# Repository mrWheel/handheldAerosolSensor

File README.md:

# Low-Power Air Quality Monitor (SPS30 + E-Paper)

## Disclaimer
This software is developed incrementally. That means I have no clear idea how it works (though it *mostly* does).

If you have questions about this software, it will probably take you just as long to figure things out as it would take me. So I’d prefer that you investigate it yourself.

Having said that **Don’t Even Think About Using It**

Seriously. Don’t.

Building this design may injure or kill you during construction, burn your house down while in use, and then—just to be thorough—explode afterward.

This is **not** a joke. This project involves **lethal voltages**. If you are not a **qualified electronics engineer**, close this repository, step away from the soldering iron, and make yourself a cup of tea.

If you decide to ignore all of the above and build it anyway, you do so **entirely at your own risk**. You are fully responsible for taking proper safety precautions. I take **zero responsibility** for anything that happens—electrically, mechanically, chemically, spiritually, or otherwise.

Also, full disclosure: I am **not** a qualified electrical engineer. I provide **no guarantees**, **no warranties**, and **absolutely no assurance** that this design is correct, safe, or suitable for any purpose whatsoever.

# What it is
This project is a **battery-powered, low-power air quality monitor** based on:

- **ESP32 DEVKIT V1**
- **Sensirion SPS30** particulate matter sensor (I²C)
- **1.54" black/white e‑paper display (200×200)**
- **High-side power latch** using a P‑channel MOSFET + 2N7000 or BSS138
- **Single-cell Li‑ion (18650)** battery with DC/DC boost to 5 V

The system powers itself on with a button, performs a measurement cycle, updates the e‑paper display, and then **fully powers itself off** to achieve near-zero standby current.

---

## Features

- True hardware power-off (no sleep leakage)
- SPS30 warm-up with countdown on e‑paper
- Configurable number of measurement attempts
- **Only valid sensor samples are averaged**
- PM1.0 / PM2.5 / PM10 display
- Simple air-quality classification (PM2.5 based)
- Battery voltage and percentage display

---

## Measurement Flow

1. User presses power button
2. Power latch engages
3. E‑paper resets and shows status
4. SPS30 starts measurement
5. Warm-up delay (default: 15 s)
6. Up to `maxMetingen` measurement attempts
   - Only valid samples are accumulated
7. Average values are calculated
8. Results are shown on the e‑paper
9. SPS30 is stopped
10. Power latch is released (device turns fully off)

---

## Hardware Connections

### ESP32 DevKit V1 - Pin mapping for AerosolSensor

| ESP32 pin | DEVKIT V1 | Standaard functie              | AerosolSensor        | Opmerking |
|-----------|-----------|--------------------------------|----------------------|-----------|
| 25        | D25       | GPIO / DAC1                    | GPIO_PIN_LATCH       | Latch control (OUTPUT) |
| 33        | D33       | GPIO / ADC1_CH5 / Touch        | GPIO_PIN_SWITCH      | Switch input (INPUT_PULLUP), non-strapping |
| 34        | D34       | ADC1_CH6 (input-only)          | GPIO_PIN_BAT_ADC     | Battery ADC (input-only), ADC1 recommended |
| 21        | D21       | I2C SDA (typical)              | GPIO_PIN_SPS30_SDA   | SPS30 SDA |
| 22        | D22       | I2C SCL (typical)              | GPIO_PIN_SPS30_SCL   | SPS30 SCL |
| 16        | RX2       | Future Ext.                    | GPIO_PIN_SPS_UART_RX | Serial SPS module |
| 17        | TX2       | Future Ext.                    | GPIO_PIN_SPS_UART_TX | Serial SPS module | 
| 23        | D23       | VSPI MOSI (typical)            | GPIO_PIN_EPD_MOSI    | E-paper DIN (MOSI) |
| -1        | n.c.      | n.v.t.                         | GPIO_PIN_EPD_MISO    | Not connected on display |
| 18        | D18       | VSPI SCK (typical)             | GPIO_PIN_EPD_SCK     | E-paper CLK (SCK) |
| 27        | D27       | GPIO                           | GPIO_PIN_EPD_CS      | E-paper CS |
| 19        | D19       | e-Paper DC                     | GPIO_PIN_EPD_DC      | E-paper DC |
| 13        | D13       | e-Paper RST                    | GPIO_PIN_EPD_RST     | E-paper RST |
| 32        | D32       | GPIO / ADC1_CH4 / Touch        | GPIO_PIN_EPD_BUSY    | E-paper BUSY (INPUT_PULLUP), non-strapping |
| 14        | D14       | GPIO PWM Touch                 | GPIO_PIN_BUZZER_PWM  | Buzzer 

### Battery Measurement

- 100 kΩ / 100 kΩ divider from battery to D34
- Optional 100 nF capacitor from D34 to GND

---

## Software Stack

- **PlatformIO**
- **Arduino framework**
- **Libraries**
  - GxEPD2
  - Adafruit GFX
  - Adafruit BMP280 Library
  - Adafruit Unified Sensor
  - Sensirion SPS30 (GitHub)
  - safeTimers

---

## PlatformIO Configuration

```ini
; platformio.ini
;
;— ESP32 + Arduino framework
;— Pin choices avoid ESP32 strapping pins (GPIO0,2,4,5,12,15) and flash pins (GPIO6–11).
;— Battery ADC uses ADC1 (GPIO34) so it keeps working even if WiFi were enabled.
;— SPI uses VSPI defaults for ESP32: MOSI=23, MISO=19, SCK=18.

[platformio]
workspace_dir = .pio.nosync
default_envs = esp32dev

[env:esp32dev]
platform = espressif32
board = esp32dev
framework = arduino

monitor_speed = 115200
upload_speed = 921600

;-- do NOT use 0, 2, 4, 5, 12, 15 (Strapping pins) or 6–11 (Flash pins)
build_flags =
  ;==================== Power & user input ====================
  ;— Power latch control (OUTPUT)
  -D GPIO_PIN_LATCH=25

  ;— User pushbutton (INPUT_PULLUP, LOW = pressed)
  -D GPIO_PIN_SWITCH=33

  ;==================== Battery measurement ====================
  ;— Battery voltage divider ADC input (ADC1)
  -D GPIO_PIN_BAT_ADC=34

  ;==================== SPS air quality sensor ====================
  ;— SPS I2C interface
  -D GPIO_PIN_SPS_SDA=21
  -D GPIO_PIN_SPS_SCL=22

  ;— SPS UART interface (UART2, hardware default pins)
  -D GPIO_PIN_SPS_UART_TX=17
  -D GPIO_PIN_SPS_UART_RX=16

  ;==================== E-paper display (SPI) ====================
  ;— SPI data pins (VSPI defaults)
  -D GPIO_PIN_EPD_MOSI=23
  -D GPIO_PIN_EPD_MISO=-1
  -D GPIO_PIN_EPD_SCK=18

  ;— E-paper control pins
  -D GPIO_PIN_EPD_CS=27
  -D GPIO_PIN_EPD_DC=19
  -D GPIO_PIN_EPD_RST=13
  -D GPIO_PIN_EPD_BUSY=32

  ;==================== User feedback ====================
  ;— Piezo buzzer (PWM via LEDC)
  -D GPIO_PIN_BUZZER_PWM=14

  ;==================== Application configuration ====================
  -D WARMUP_SECONDS=5
  -D MAX_METINGEN=5

  ;==================== ADC calibration ====================
  -D ADC_VREF_VOLTAGE=3.30f
  
  ;==================== Battery calibration ====================
  -D BAT_CAL_GAIN=0.94245f
  -D BAT_CAL_OFFSET=0.48763f

  ;==================== Library configuration ====================
  -D DISABLE_DIAGNOSTIC_OUTPUT

lib_deps =
  zinggjm/GxEPD2@^1.6.5
  adafruit/Adafruit GFX Library@^1.11.9
  adafruit/Adafruit BMP280 Library
	adafruit/Adafruit Unified Sensor
  https://github.com/Sensirion/arduino-sps.git
  https://github.com/mrWheel/safeTimers.git
```

---

## Power Latch Notes

- Upload firmware with **stable power** (USB directly)
- During normal operation the latch cuts power completely
- GPIO D25 must be set HIGH early in `setup()` to hold power

---

## Customization

You can easily adjust:

- `warmupSeconds` (e.g. 15 → 30)
- `maxMetingen` (e.g. 5 → 10)
- PM2.5 thresholds for status classification
- Display layout and fonts

---

## License

This project is intended for personal and educational use.
You are free to modify and adapt it for your own hardware.

---

## Notes

This design prioritizes:
- Measurement correctness
- Ultra-low standby power
- Robust behavior on battery power

It is well suited for **portable or infrequently-used air quality measurements** where long battery life matters.

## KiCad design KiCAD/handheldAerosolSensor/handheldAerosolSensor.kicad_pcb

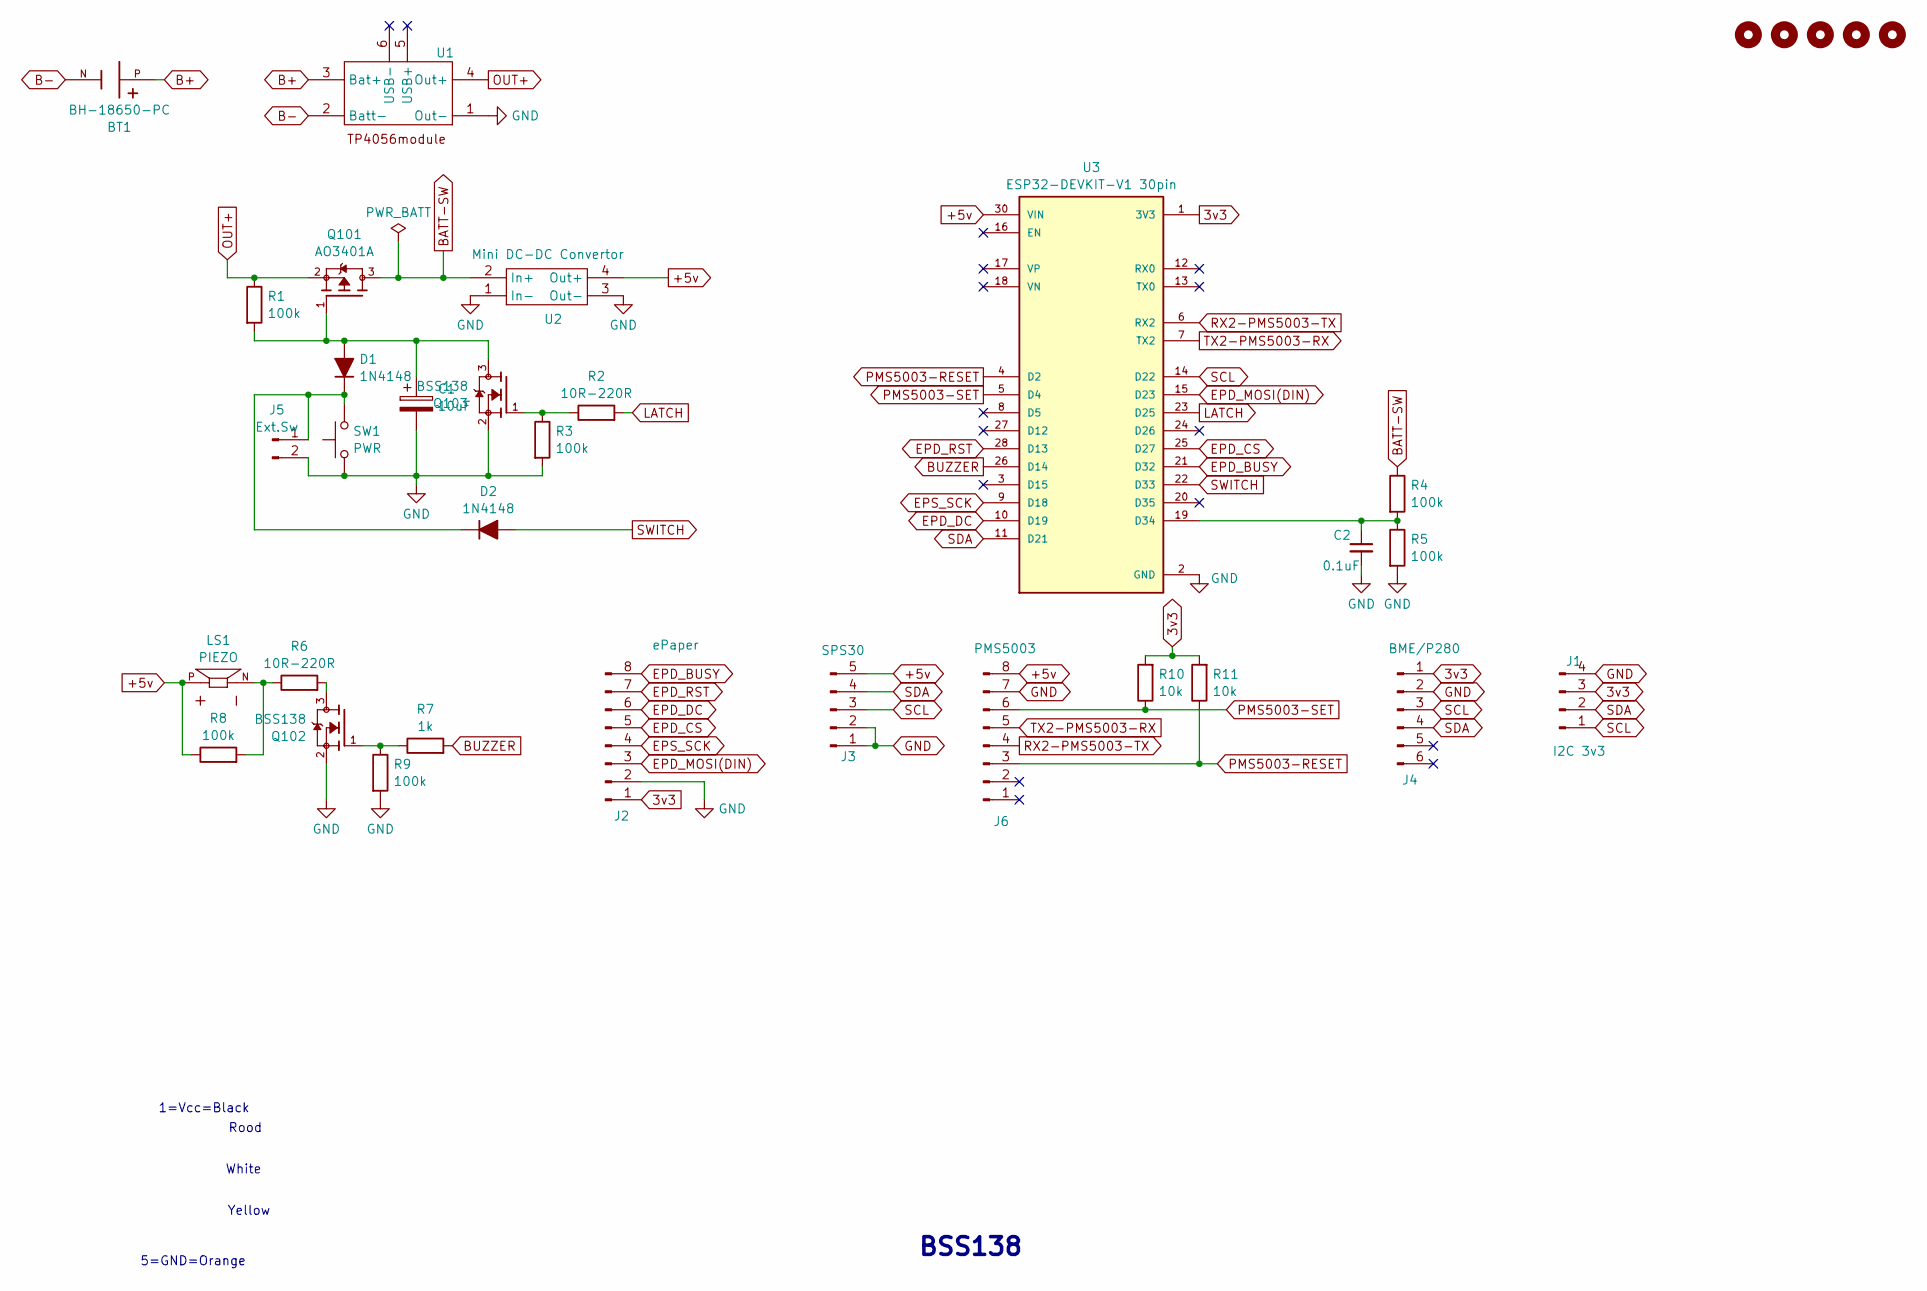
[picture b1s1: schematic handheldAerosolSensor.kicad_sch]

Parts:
BT1: BH-18650-PC; BAT_BH-18650-PC; PARTREV 05/17/19
C1: 10uF; C_1206_3216Metric_Pad1.33x1.80mm_HandSolder
C2: 0.1uF; C_1206_3216Metric_Pad1.33x1.80mm_HandSolder
D1, D2: 1N4148; D_1206_3216Metric_Pad1.42x1.75mm_HandSolder
H1, H2, H3, H4, H5: MountingHole; MountingHole_2.7mm
J1: I2C 3v3; JST_XH_B4B-XH-A_1x04_P2.50mm_Vertical
J2: ePaper; JST_XH_B8B-XH-A_1x08_P2.50mm_Vertical
J3: SPS30; JST_XH_B5B-XH-A_1x05_P2.50mm_Vertical
J4: BME/P280; PinSocket_1x06_P2.54mm_Vertical
J5: Ext.Sw; JST_XH_B2B-XH-A_1x02_P2.50mm_Vertical
J6: PMS5003; JST_XH_B8B-XH-A_1x08_P2.50mm_Vertical
LS1: PIEZO; XDCR_CPI-148-24-90T-67; PARTREV 1
Q101: AO3401A; AO3401
Q102, Q103: BSS138; PARTREV 30 Jan 2018
R1, R3, R4, R5, R8, R9: 100k; R_1206_3216Metric_Pad1.30x1.75mm_HandSolder
R2, R6: 10R-220R; R_1206_3216Metric_Pad1.30x1.75mm_HandSolder
R7: 1k; R_1206_3216Metric_Pad1.30x1.75mm_HandSolder
R10, R11: 10k; R_1206_3216Metric_Pad1.30x1.75mm_HandSolder
SW1: PWR; SW_PUSH_6mm_H4.3mm
U1: TP4056_USB-Charger_Board
U2: Mini DC-DC Convertor; Mini DC-DC Boost Convertor
U3: ESP32-DEVKIT-V1 30pin; MODULE_ESP32_DEVKIT_V1_30pin; PARTREV N/A

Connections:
3v3: J1.3, J2.1, J4.1, R10.2, R11.2, U3.1 (3V3)
+5v: J3.5, J6.8, LS1.P, R8.1, U2.4 (Out+), U3.30 (VIN)
B+: BT1.P, U1.3 (Bat+)
B-: BT1.N, U1.2 (Batt-)
BATT-SW: Q101.3, R4.1, U2.2 (In+)
BUZZER: R7.2, U3.26 (D14)
EPD_BUSY: J2.8, U3.21 (D32)
EPD_CS: J2.5, U3.25 (D27)
EPD_DC: J2.6, U3.10 (D19)
EPD_MOSI(DIN): J2.3, U3.15 (D23)
EPD_RST: J2.7, U3.28 (D13)
EPS_SCK: J2.4, U3.9 (D18)
GND: C1.2, C2.2, J1.4, J2.2, J3.1, J3.2, J4.2, J5.2, J6.7, Q102.2, Q103.2, R3.2, R5.2, R9.2, SW1.1, U1.1 (Out-), U2.1 (In-), U2.3 (Out-), U3.2 (GND), U3.29 (GND)
LATCH: R2.2, U3.23 (D25)
unnamed: C1.1, D1.2 (A), Q101.1, Q103.3, R1.2
unnamed: D1.1 (K), D2.1 (K), J5.1, SW1.2
unnamed: LS1.N, R6.1, R8.2
unnamed: Q102.1, R7.1, R9.1
unnamed: Q102.3, R6.2
unnamed: Q103.1, R2.1, R3.1
unnamed: C2.1, R4.2, R5.1, U3.19 (D34)
OUT+: Q101.2, R1.1, U1.4 (Out+)
PMS5003-RESET: J6.3, R11.1, U3.4 (D2)
PMS5003-SET: J6.6, R10.1, U3.5 (D4)
RX2-PMS5003-TX: J6.4, U3.6 (RX2)
SCL: J1.1, J3.3, J4.3, U3.14 (D22)
SDA: J1.2, J3.4, J4.4, U3.11 (D21)
SWITCH: D2.2 (A), U3.22 (D33)
TX2-PMS5003-RX: J6.5, U3.7 (TX2)

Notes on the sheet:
1=Vcc=Black
Rood
BSS138
5=GND=Orange
Yellow
White

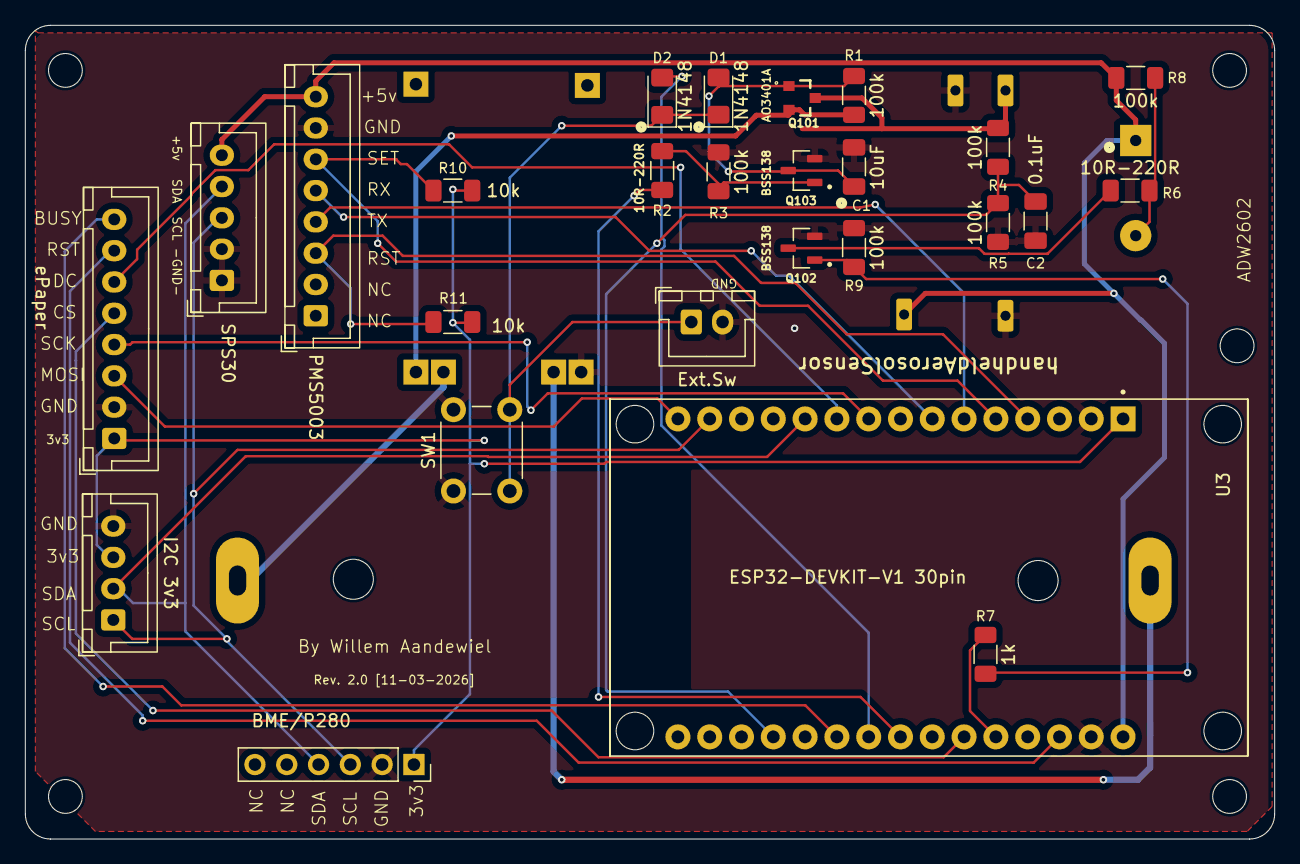
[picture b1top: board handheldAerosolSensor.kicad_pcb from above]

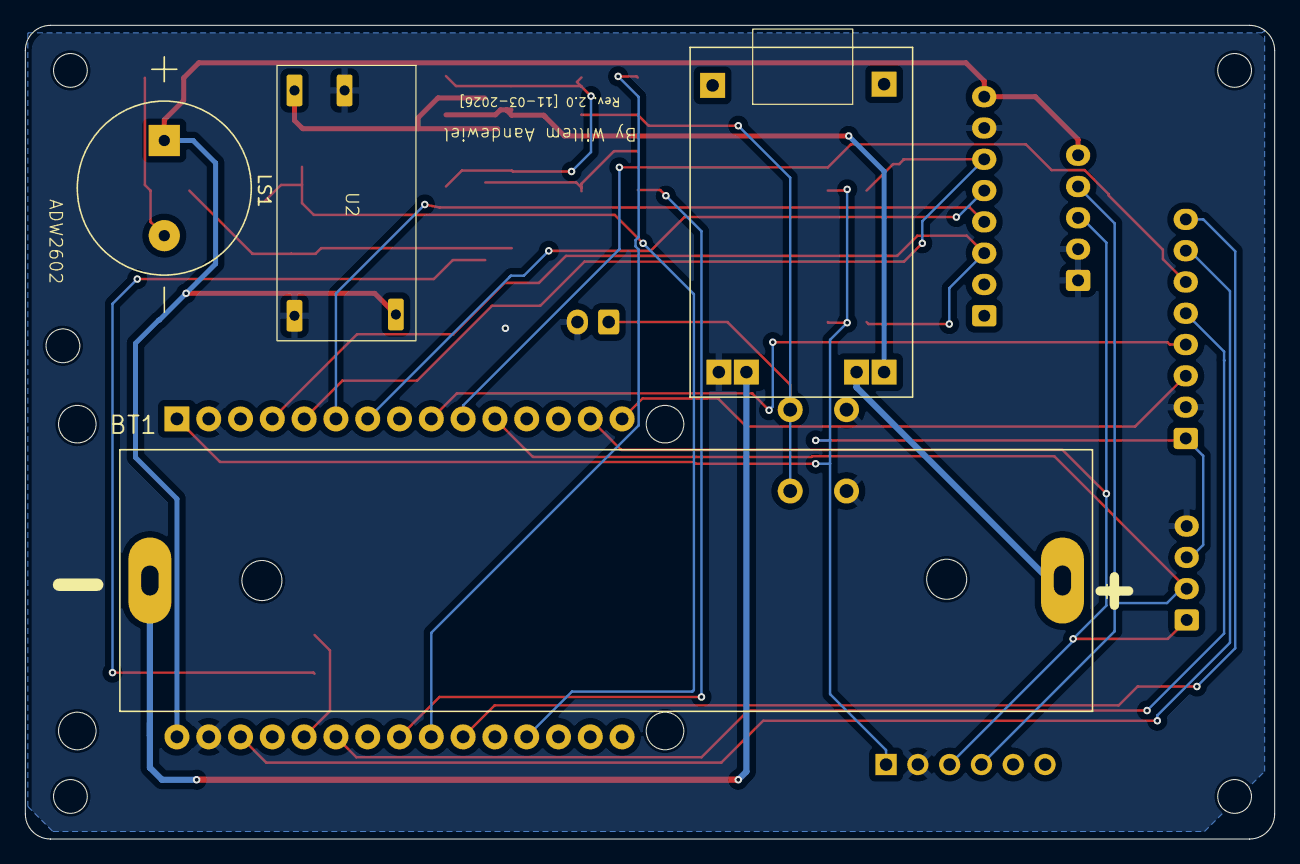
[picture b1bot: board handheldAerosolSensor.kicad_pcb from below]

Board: 2 copper layers, 99.8 x 65.0 mm, 35 parts (4 on the bottom side), 29 nets.

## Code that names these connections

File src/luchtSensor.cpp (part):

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
// ===================== User configuration =====================

// Latch control pin (drives the 2N7000 gate through a series resistor)
static const uint8_t PIN_LATCH = GPIO_PIN_LATCH;

// Pushbutton pin to release the latch or do other things
static const uint8_t PIN_SWITCH = GPIO_PIN_SWITCH;

// Battery divider ADC input (100k/100k => ADC sees Vbat/2)
static const uint8_t PIN_BAT_ADC = GPIO_PIN_BAT_ADC;

// E-paper pins (SPI on Nano: MOSI=D11, SCK=D13 are fixed by hardware SPI)
static const uint8_t PIN_EPD_CS = 10;
static const uint8_t PIN_EPD_DC = 9;
static const uint8_t PIN_EPD_RST = 8;
static const uint8_t PIN_EPD_BUSY = 7;

// Warm-up time after starting SPS30 measurement
static const uint16_t warmupSeconds = WARMUP_SECONDS;
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static const uint16_t PAGE_HEIGHT = (MAX_DISPLAY_BUFFER_SIZE / (200 / 8)); // 32

GxEPD2_BW<GxEPD2_154_D67, PAGE_HEIGHT> display(
  GxEPD2_154_D67(PIN_EPD_CS, PIN_EPD_DC, PIN_EPD_RST, PIN_EPD_BUSY)
);
//GxEPD2_BW<GxEPD2_154, PAGE_HEIGHT> display(
//  GxEPD2_154(PIN_EPD_CS, PIN_EPD_DC, PIN_EPD_RST, PIN_EPD_BUSY)
//);

// ===================== Air quality classification =====================
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{
  Serial.flush();

  digitalWrite(PIN_LATCH, LOW);

  while(true) 
  {
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
void setup()
{
  // Latch the power as early as possible to avoid dropping out during boot.
  pinMode(PIN_LATCH, OUTPUT);
  digitalWrite(PIN_LATCH, HIGH);

  pinMode(LED_BUILTIN, OUTPUT);
  pinMode(PIN_SWITCH, INPUT_PULLUP);

  for(int i=0; i<5; i++) 
  {
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
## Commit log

2026-02-06 v0.2.4
2026-02-06 v0.2.5 - test new tag-release.yml
2026-02-06 v1.0.0 - still testing tag-release.yml
2026-02-06 v1.0.1 -bug fix
2026-02-07 feat: migrate from Arduino Nano to ESP32 platform
    Migrate the entire project from ATmega328 (Arduino Nano) to ESP32
    development board to enable future expansion capabilities.
    Key changes:
    - Update platformio.ini to target esp32dev board with espressif32 platform
    - Remap all GPIO pins to ESP32-safe pins (avoiding strapping pins GPIO0,2,4,5,12,15)
    - Use VSPI defaults for e-paper display (MOSI=23, MISO=19, SCK=18)
2026-02-07 feat: add EPD geometry diagnostic test and bump version to v0.1.1
    Added epdGeometryTest() function to diagnose and visualize e-paper
    display dimensions and coordinate system. The test draws:
    - Outer and inner border rectangles
    - Center crosshair for alignment verification
    - Horizontal guide lines at 20px intervals
    - Corner coordinates and dimension labels
2026-02-07 Changed version from v0.1.1 to v0.2.1
2026-02-07 Constant PROG_VERSION was rotten
2026-02-07 refactor: rollback version and standardize code formatting
    - Rollback version from v0.2.2 to v0.2.0
    - Standardize comment style from `// —` to `//--` throughout
    - Change EPD pin types from uint8_t to int8_t for consistency
    - Add warning comments to protect PROG_VERSION variable name
    - Reformat code structure and improve whitespace consistency
2026-02-08 feat: refactor GPIO configuration and add SPS30 UART support
    - Reorganize platformio.ini GPIO definitions with clear sections and improved comments
    - Add SPS30 UART interface support (GPIO 16/17) alongside existing I2C
    - Remap e-paper display control pins (DC: 17→19, RST: 16→13) to free UART2 pins
    - Add buzzer PWM pin (GPIO 14) for user feedback
    - Increase warmup time (3→5s) and max measurements (2→5)
    - Reduce long-press threshold from 5s to 2s for better UX
2026-02-08 feat: add BME280 environmental sensor support
    Add temperature, humidity, and pressure monitoring using Adafruit BME280 sensor. Updates include:
    - Add Adafruit BME280 and Unified Sensor library dependencies
    - Integrate BME280 sensor initialization and data reading
    - Update display layout to show environmental data alongside particle measurements
    - Rename SPS30 references to generic SPS for broader sensor compatibility
    - Refactor comment style for consistency throughout codebase
2026-02-08 feat: switch to BMP280 sensor and add battery calibration
    - Replace BME280 with BMP280 sensor library and implementation
    - Add battery voltage calibration constants (gain: 0.94245, offset: 0.48763)
    - Add comprehensive safety warnings to README about lethal voltages
    - Fix typo in README ("Disclamer" → "Disclaimer")
    - Update pre-shutdown routine to include environment sensor readings
    - Adjust ADC reference voltage to 3.30V
2026-02-08 docs: update GPIO pin mappings and add BMP280 sensor support
    - Reassign e-Paper DC (GPIO17→19) and RST (GPIO16→13) pins to free UART2
    - Reserve GPIO16/17 (RX2/TX2) for future serial SPS module extension
    - Add GPIO14 for buzzer PWM control
    - Include Adafruit BMP280 and Unified Sensor libraries
    - Update battery ADC documentation from A0 to D34
    - Simplify platformio.ini documentation section
2026-02-08 docs: add complete platformio.ini configuration to README
    - Add comprehensive platformio.ini example with detailed GPIO pin mappings
    - Document all build flags for power, battery, sensors, display, and buzzer
    - Include application and calibration configuration parameters
    - Add complete library dependencies section
    - Fix indentation for Adafruit Unified Sensor in dependency list
2026-02-08 feat: add audio feedback for power latch state transitions
    Add two-tone beep system to provide audible feedback during device power
    state changes:
    - Beep on startup when latch is fixed (900Hz -> 1100Hz)
    - Beep before shutdown when latch is disabled (1100Hz -> 900Hz)
    Implemented playTwoToneBeep() helper function with configurable frequency,
    duration, and gap parameters. This improves user experience by providing
2026-02-08 chore: make git hook script executable and fix whitespace
    - Set executable permissions on bumpProgVersion.py git hook
    - Remove trailing whitespace from Display comment in main.cpp
    The git hook script needs to be executable to function properly when
    triggered by git events.
2026-02-08 Test bumpProgVersion
2026-02-09 feat: enhance template application with smart file comparison
    - Add comprehensive file comparison strategies (hash, size, mtime, lines, diff)
    - Add smart normalization for tag-release.yml to ignore project-specific values
    - Introduce unified diff generation for reviewing changes
    - Add backup file path generation utilities
    - Fix typo in default paths: .clangFormat → .clang-format
    This enhancement enables the template application script to intelligently
2026-02-10 refactor: improve version management script and buzzer functionality
    - Refactor playTwoToneBeep() to use separate duration parameters for each tone
    - Adjust beep frequencies (700/1500 Hz) and timings for clearer audio feedback
    - Ensure buzzer pin is HIGH when inactive to prevent buzzing
    - Enhance bumpProgVersion.py with automatic version file detection
    - Add support for tracking all source files, not just staged ones
    - Improve JSON handling with versionFile field for better tracking
2026-02-10 Add version date comment to applyTemplate.py
2026-02-10 Translate warning messages to English
2026-02-10 Added applyTemplate.py in sync
2026-02-10 Added KiCAD
2026-02-11 feat(hardware): Add buzzer and reorganize PCB net naming
    - Add CPI-148-24-90T-67 buzzer/transducer component (LS1)
    - Refactor battery net names for consistency (BAT → BATT, BATT-SW)
    - Reorganize net numbering and clean up net naming scheme
    - Update component references and power connections
    - Add new footprint library entry for buzzer transducer
2026-02-11 feat(kicad): add image to handheld aerosol sensor schematic
2026-02-11 Replace placeholder values in GitHub Actions workflow with actual project configuration. Updates PROGRAM_NAME to "handheldAerosolSensor" and sets correct paths for PROGRAM_SRC (main.cpp) and PROGRAM_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
2026-02-11 refactor(sensors): migrate to official Sensirion libraries and improve I2C
    - Replace GitHub URL dependency with official Sensirion Core and SPS libraries from registry
    - Add I2C timeout (50ms) to prevent rare ESP32 bus deadlocks
    - Initialize Sensirion I2C driver binding during I2C setup
    - Enhance I2C scan with device counter and improved error handling
    - Remove unused diagnostic functions (i2cReadReg8, logBmpChipId)
    - Clean up code formatting and remove test/debug artifacts
2026-02-11 feat: add SPS30 test environment and debug logging
    **Changes:**
    - Refactored platformio.ini to support multiple build environments
    - Extracted common settings into shared [env] section
    - Created new esp32dev_testSPS30 environment for SPS30 testing
    - Added src_filter to control compilation of main.cpp vs testSPS30.cpp
    - Cleaned up comments and improved formatting
2026-02-11 Many inprovements
2026-02-11 Refactor loop()
2026-02-11 Refactor ePaper layout
2026-02-11 refactor(ui): redesign PM display to column-based layout
    Major UI redesign and configuration adjustments:
    **Display Layout:**
    - Restructure PM values display from row-based to column-based format
    - Replace separate yPm1/yPm25/yPm10 positions with unified yPmHeader/yPmValues
    - Change PM layout from xPmLabel/xPmValue to xPmCol1/xPmCol2/xPmCol3
    - Add FreeMonoBold18pt7b font for larger value display
2026-02-15 KiCad aanpassingen
2026-02-15 Add power indicator LED (D201) with supporting components to the PCB design: - Add 1206 SMD power LED with current limiting resistor - Add new nets for LED connections (Net-(C201-Pad1), Net-(D201-A))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
2026-02-15 Repositioned all mounting holes (H1-H5, H201-H204) to align with updated mechanical constraints. Updated board edge graphics and coordinates to match the new hole positions. Changes improve PCB fitme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
2026-03-08 - Refactor sensor code from SPS UART to PMS5003 UART throughout main.cpp - Add displayRefreshInProgress flag for better UI state tracking - Update pin naming conventions to reflect PMS5003 hardware
2026-03-08 Updated program version from v0.9.0 to v0.9.1 in main.cpp.
2026-03-08 feat: improve PM value display formatting with tiered precision
    Updated formatPmLine() to display particulate matter values with
    context-appropriate precision:
    - Values <100: shown with one decimal place (e.g., "45.3")
    - Values 100-999: shown as integers (e.g., "342")
    - Values >999: capped at "999" to prevent display overflow
    This improves readability and makes better use of limited display
2026-03-08 feat: add configurable e-paper display rotation
    Add E_PAPER_ROTATION build flag to allow configuring display orientation
    (0-3) with validation and fallback to default rotation. Also adjust PM
    sensor validation limits from 2000 to 1000 µg/m³ for more realistic
    range checking.
    - Add E_PAPER_ROTATION build flag in platformio.ini (default: 0)
    - Implement rotation validation in epdInit() with fallback to rotation 1
2026-03-12 KiCAD design openScad design
2026-03-12 KiCAD changed
2026-03-13 Major version release with the following changes: - Add ePaper display PCB configuration and mounting cutouts - Update PCB reference file name to handheldAerosolSensorPCB.stl - Refine cutout dimensio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
2026-03-13 Add support for PMS5003 sensor as an alternative to SPS30: - Introduce ParticleSensorType enum to distinguish between sensor types - Add PMS5003 pin definitions (SET, RESET) and control functions - I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
2026-03-13 - Add battery protection at startup (shutdown if < 3.4V) - Display "BATTERY LOW" warning before shutdown when < 3.6V - Store last battery voltage/percentage for later checks - Fix message area partia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
2026-03-13 Add WiFi configuration and Over-The-Air (OTA) update capabilities to the handheld aerosol sensor:
    - Add WiFiManager library dependency for WiFi credential management
    - Create new PlatformIO environment (esp32dev_ota) for OTA uploads
    - Implement WiFi portal UI screen to guide users during configuration
    - Add OTA update waiting screen with hostname and IP display
    - Consolidate PlatformIO environments by removing separate test configurations
    - Add WiFi erase build flag option for resetting credentials
2026-03-13 - Bump version from v0.10.3 to v1.0.0 in firmware - Reorganize 3D model file paths to documents directory - Add ePaper display model reference for visualization - Adjust ePaper display cutout positio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
